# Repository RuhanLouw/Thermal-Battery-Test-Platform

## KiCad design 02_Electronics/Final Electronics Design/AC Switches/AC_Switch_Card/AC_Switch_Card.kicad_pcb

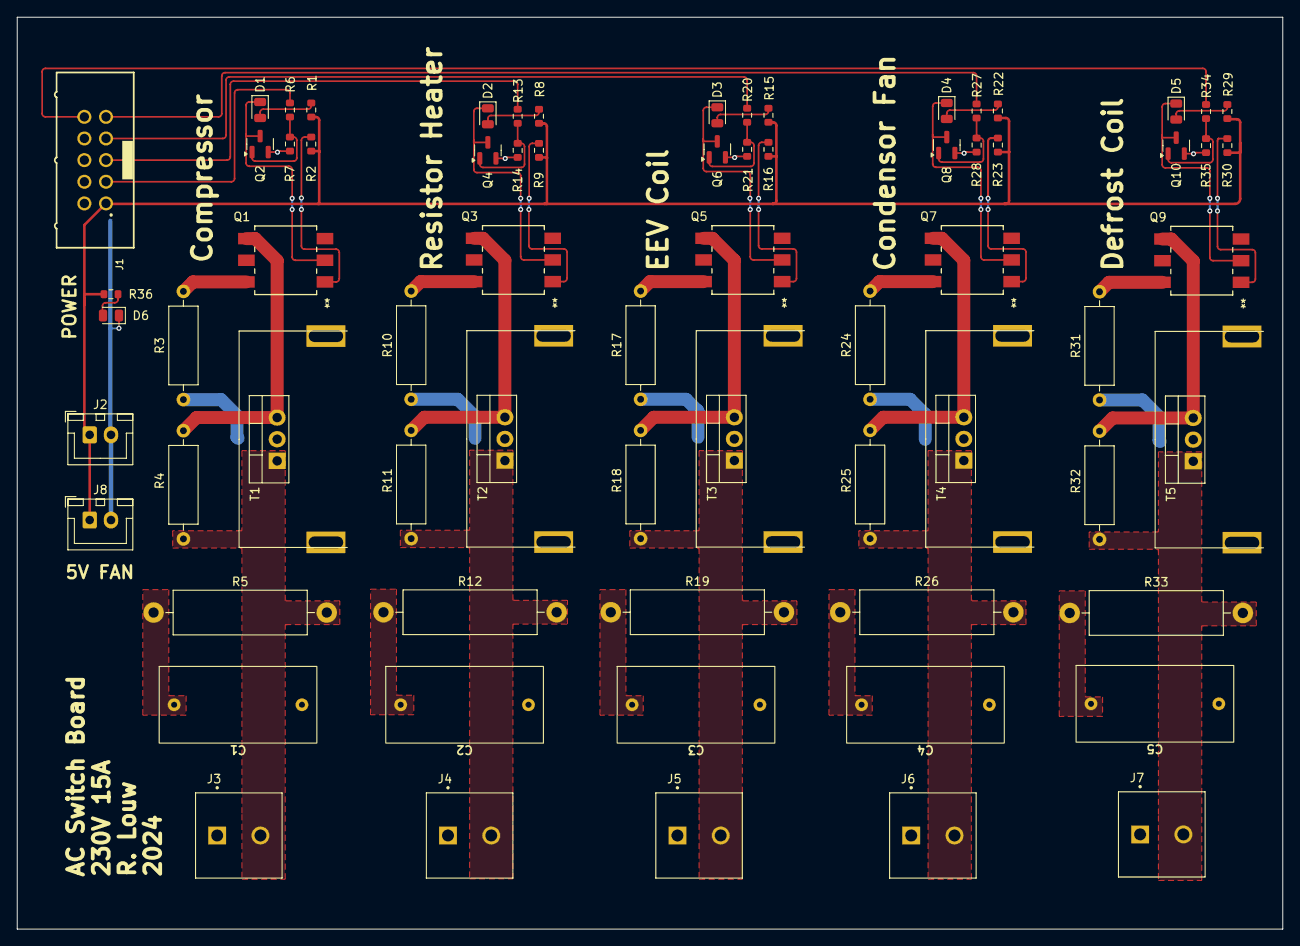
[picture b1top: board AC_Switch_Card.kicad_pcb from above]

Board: 2 copper layers, 148.5 x 107.0 mm, 70 parts (0 on the bottom side), 53 nets.

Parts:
C1, C2, C3, C4, C5: 0.22u; CAP FILM 0.22UF 10 800VDC RAD
D1, D2, D3, D4, D5, D6: LED RED CLEAR 0805 SMD; LED_0805_2012Metric
J1: Control IN; 61201021621
J2, J8: Fan; JST_XH_B2B-XH-A_1x02_P2.50mm_Vertical
J3, J4, J5, J6, J7: Screw_Terminal_01x02; TE_282857-2_screw
Q1, Q3, Q5, Q7, Q9: MOC3063S-TA1; MOC306XS_LTO
Q2, Q4, Q6, Q8, Q10: BSS138L; SOT-23
R1, R8, R15, R22, R29, R36: 145; R_0603_1608Metric
R2, R9, R16, R23, R30: 182; R_0603_1608Metric
R3, R10, R17, R24, R31: 100; R_Axial_DIN0309_L9.0mm_D3.2mm_P12.70mm_Horizontal
R4, R11, R18, R25, R32: 390; R_Axial_DIN0309_L9.0mm_D3.2mm_P12.70mm_Horizontal
R5, R12, R19, R26, R33: 51; R_Axial_DIN0516_L15.5mm_D5.0mm_P20.32mm_Horizontal
R6, R13, R20, R27, R34: 300; R_0603_1608Metric
R7, R14, R21, R28, R35: 10k; R_0603_1608Metric
T1, T2, T3, T4, T5: BT138-800E,127; HSS-B20-NPR-02 heatsink

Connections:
5V_{DD}: J1.1, J2.1, J8.1, R1.2, R2.1, R8.2, R9.1, R15.2, R16.1, R22.2, R23.1, R29.2, R30.1, R36.2
/AC_SWITCH1/230VAC: C2.2, J4.1, R10.1, T2.2
/AC_SWITCH1/LOAD: J4.2, R11.2, R12.2, T2.1
/AC_SWITCH2/230VAC: C3.2, J5.1, R17.1, T3.2
/AC_SWITCH2/LOAD: J5.2, R18.2, R19.2, T3.1
/AC_SWITCH3/230VAC: C4.2, J6.1, R24.1, T4.2
/AC_SWITCH3/LOAD: J6.2, R25.2, R26.2, T4.1
/AC_SWITCH4/230VAC: C5.2, J7.1, R31.1, T5.2
/AC_SWITCH4/LOAD: J7.2, R32.2, R33.2, T5.1
/AC_SWITCH/230VAC: C1.2, J3.1, R3.1, T1.2
/AC_SWITCH/LOAD: J3.2, R4.2, R5.2, T1.1
AC COMP ENABLE: J1.3, R6.1
AC DEFROST ENABLE: J1.10, R34.1
AC EEV COIL ENABLE: J1.7, R20.1
AC FAN ENABLE: J1.9, R27.1
AC HEATER RESISTOR ENABLE: J1.5, R13.1
GND_{DD}: D6.1 (K), J1.2, J2.2, J8.2, Q2.2 (S), Q4.2 (S), Q6.2 (S), Q8.2 (S), Q10.2 (S), R7.2, R14.2, R21.2, R28.2, R35.2
unnamed: C1.1, R5.1
unnamed: C2.1, R12.1
unnamed: C3.1, R19.1
unnamed: C4.1, R26.1
unnamed: C5.1, R33.1
unnamed: D1.2 (A), R1.1
unnamed: D1.1 (K), Q1.2, Q2.3 (D)
unnamed: D2.2 (A), R8.1
unnamed: D2.1 (K), Q3.2, Q4.3 (D)
unnamed: D3.2 (A), R15.1
unnamed: D3.1 (K), Q5.2, Q6.3 (D)
unnamed: D4.2 (A), R22.1
unnamed: D4.1 (K), Q7.2, Q8.3 (D)
unnamed: D5.2 (A), R29.1
unnamed: D5.1 (K), Q9.2, Q10.3 (D)
unnamed: D6.2 (A), R36.1
unnamed: Q1.1, R2.2
unnamed: Q1.4, R4.1, T1.3
unnamed: Q1.6, R3.2
unnamed: Q2.1 (G), R6.2, R7.1
unnamed: Q3.1, R9.2
unnamed: Q3.4, R11.1, T2.3
unnamed: Q3.6, R10.2
unnamed: Q4.1 (G), R13.2, R14.1
unnamed: Q5.1, R16.2
unnamed: Q5.4, R18.1, T3.3
unnamed: Q5.6, R17.2
unnamed: Q6.1 (G), R20.2, R21.1
unnamed: Q7.1, R23.2
unnamed: Q7.4, R25.1, T4.3
unnamed: Q7.6, R24.2
unnamed: Q8.1 (G), R27.2, R28.1
unnamed: Q9.1, R30.2
unnamed: Q9.4, R32.1, T5.3
unnamed: Q9.6, R31.2
unnamed: Q10.1 (G), R34.2, R35.1

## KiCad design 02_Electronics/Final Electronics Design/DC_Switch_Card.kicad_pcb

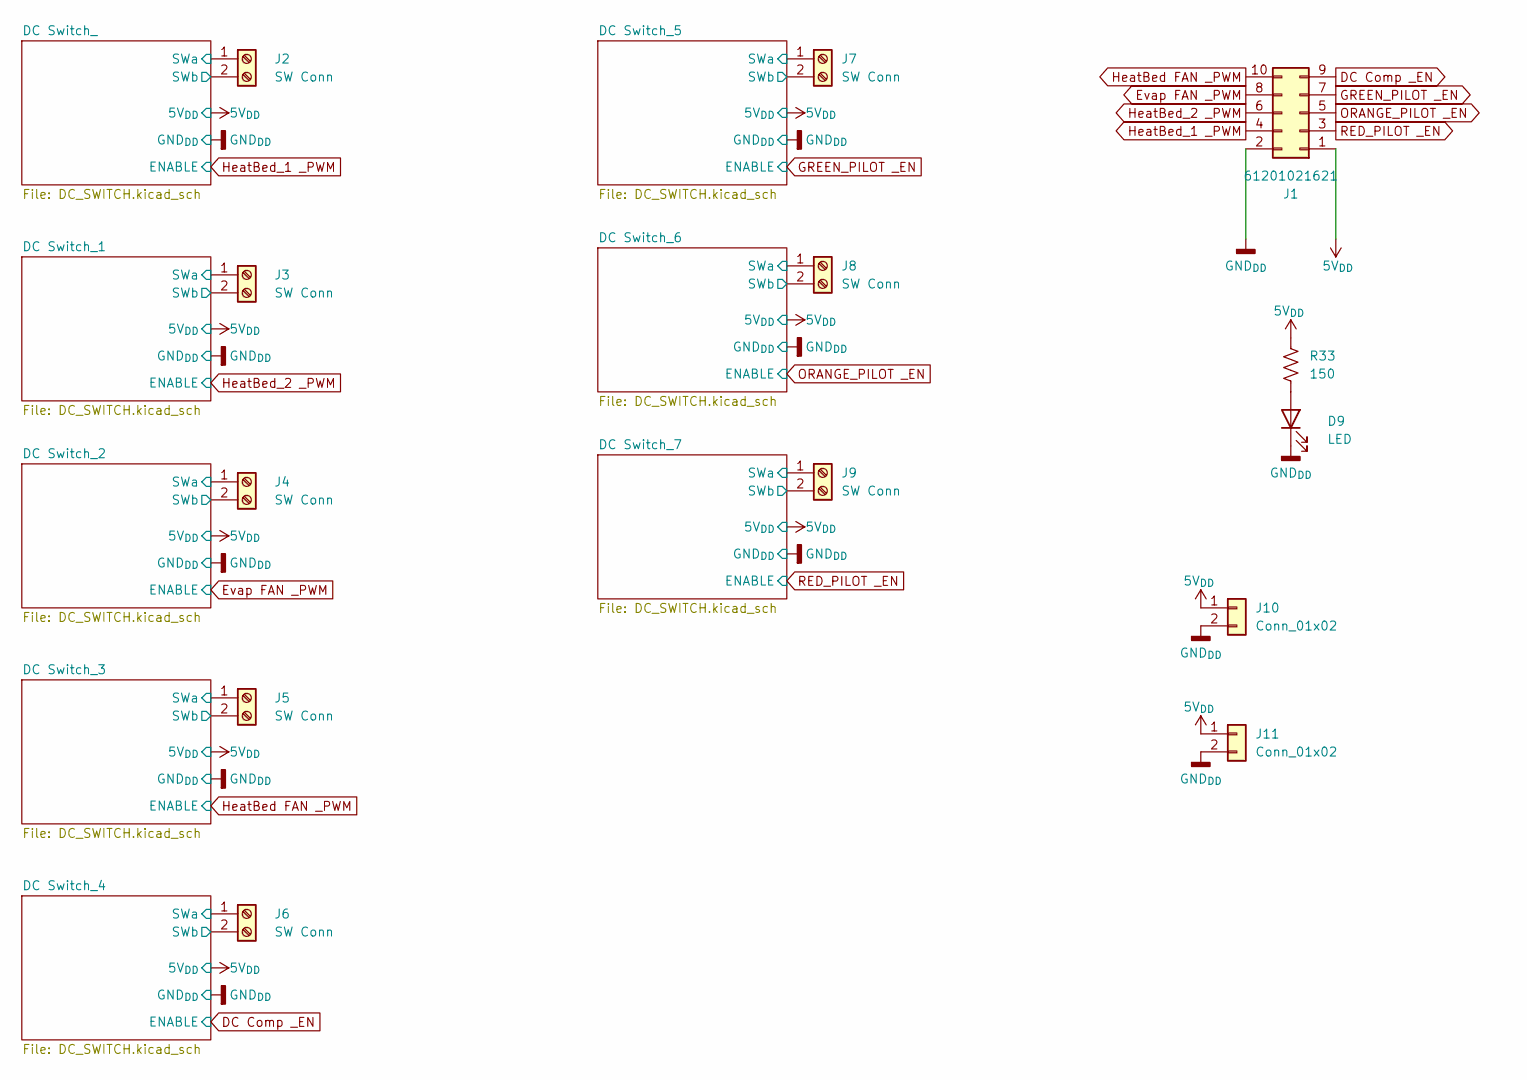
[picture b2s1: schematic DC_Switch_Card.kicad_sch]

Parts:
D9: LED; R_0805_2012Metric
J1: 61201021621
J2, J3, J4, J5, J6, J7, J8, J9: SW Conn; TE_282857-2_screw
J10, J11: Conn_01x02; JST_XH_B2B-XH-A_1x02_P2.50mm_Vertical
R33: 150; R_0603_1608Metric

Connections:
5V_{DD}: J1.1, J10.1, J11.1, R33.2; also elsewhere on the board
/DC Switch_1/SWa: J3.1; also elsewhere on the board
/DC Switch_1/SWb: J3.2; also elsewhere on the board
/DC Switch_2/SWa: J4.1; also elsewhere on the board
/DC Switch_2/SWb: J4.2; also elsewhere on the board
/DC Switch_3/SWa: J5.1; also elsewhere on the board
/DC Switch_3/SWb: J5.2; also elsewhere on the board
/DC Switch_4/SWa: J6.1; also elsewhere on the board
/DC Switch_4/SWb: J6.2; also elsewhere on the board
/DC Switch_5/SWa: J7.1; also elsewhere on the board
/DC Switch_5/SWb: J7.2; also elsewhere on the board
/DC Switch_6/SWa: J8.1; also elsewhere on the board
/DC Switch_6/SWb: J8.2; also elsewhere on the board
/DC Switch_7/SWa: J9.1; also elsewhere on the board
/DC Switch_7/SWb: J9.2; also elsewhere on the board
/DC Switch_/SWa: J2.1; also elsewhere on the board
/DC Switch_/SWb: J2.2; also elsewhere on the board
DC Comp _EN: J1.9; also elsewhere on the board
Evap FAN _PWM: J1.8; also elsewhere on the board
GND_{DD}: D9.1 (K), J1.2, J10.2, J11.2; also elsewhere on the board
GREEN_PILOT _EN: J1.7; also elsewhere on the board
HeatBed FAN _PWM: J1.10; also elsewhere on the board
HeatBed_1 _PWM: J1.4; also elsewhere on the board
HeatBed_2 _PWM: J1.6; also elsewhere on the board
unnamed: D9.2 (A), R33.1
ORANGE_PILOT _EN: J1.5; also elsewhere on the board
RED_PILOT _EN: J1.3; also elsewhere on the board

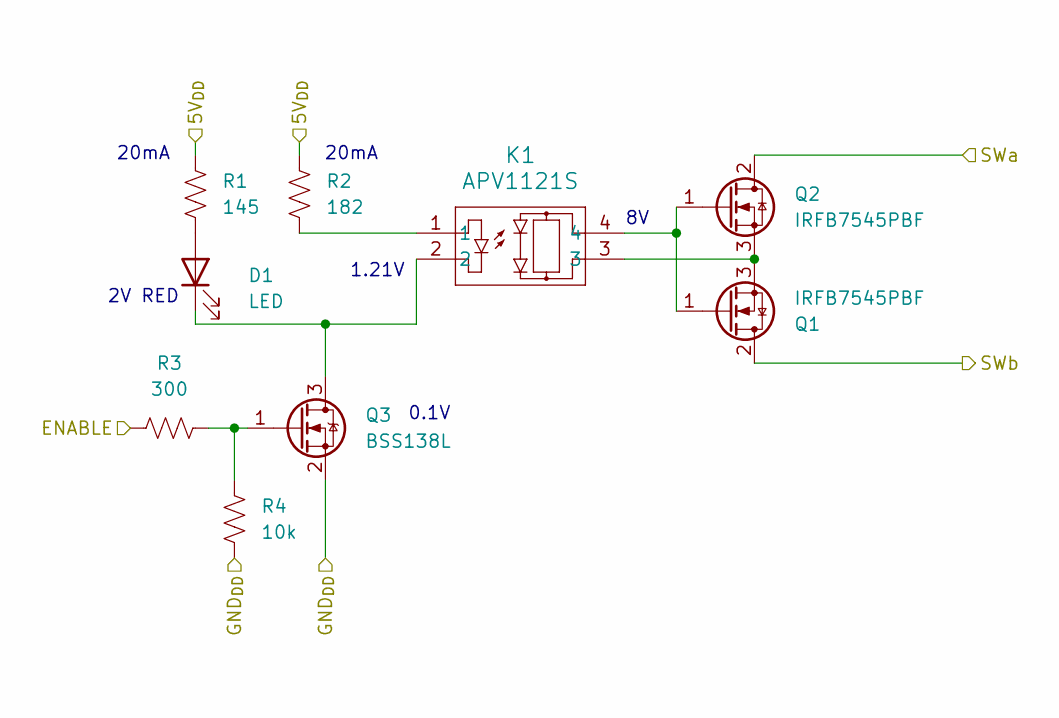
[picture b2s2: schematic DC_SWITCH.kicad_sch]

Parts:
D1: LED; R_0805_2012Metric
K1: APV1121S; SOP4PIN_PAN-M
Q1, Q2: IRFB7545PBF; TO-220-3_Vertical
Q3: BSS138L; SOT-23
R1: 145; R_0603_1608Metric
R2: 182; R_0603_1608Metric
R3: 300; R_0603_1608Metric
R4: 10k; R_0603_1608Metric

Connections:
5V_{DD}: R1.2, R2.1; also elsewhere on the board
/DC Switch_/SWa: Q2.2 (D); also elsewhere on the board
/DC Switch_/SWb: Q1.2 (D); also elsewhere on the board
GND_{DD}: Q3.2 (S), R4.2; also elsewhere on the board
HeatBed_1 _PWM: R3.1; also elsewhere on the board
unnamed: D1.2 (A), R1.1
unnamed: D1.1 (K), K1.2, Q3.3 (D)
unnamed: K1.1, R2.2
unnamed: K1.4, Q1.1 (G), Q2.1 (G)
unnamed: K1.3, Q1.3 (S), Q2.3 (S)
unnamed: Q3.1 (G), R3.2, R4.1

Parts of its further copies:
D2, D3, D4, D5, D6, D7, D8: LED; R_0805_2012Metric
K2, K3, K4, K5, K6, K7, K8: APV1121S; SOP4PIN_PAN-M
Q4, Q5, Q7, Q8, Q10, Q11, Q13, Q14, Q16, Q17, Q19, Q20, Q22, Q23: IRFB7545PBF; TO-220-3_Vertical
Q6, Q9, Q12, Q15, Q18, Q21, Q24: BSS138L; SOT-23
R5, R9, R13, R17, R21, R25, R29: 145; R_0603_1608Metric
R6, R10, R14, R18, R22, R26, R30: 182; R_0603_1608Metric
R7, R11, R15, R19, R23, R27, R31: 300; R_0603_1608Metric
R8, R12, R16, R20, R24, R28, R32: 10k; R_0603_1608Metric

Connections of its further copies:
5V_{DD}: R5.2, R6.1, R9.2, R10.1, R13.2, R14.1, R17.2, R18.1, R21.2, R22.1, R25.2, R26.1, R29.2, R30.1; also elsewhere on the board
/DC Switch_1/SWa: Q5.2 (D); also elsewhere on the board
/DC Switch_1/SWb: Q4.2 (D); also elsewhere on the board
/DC Switch_2/SWa: Q8.2 (D); also elsewhere on the board
/DC Switch_2/SWb: Q7.2 (D); also elsewhere on the board
/DC Switch_3/SWa: Q11.2 (D); also elsewhere on the board
/DC Switch_3/SWb: Q10.2 (D); also elsewhere on the board
/DC Switch_4/SWa: Q14.2 (D); also elsewhere on the board
/DC Switch_4/SWb: Q13.2 (D); also elsewhere on the board
/DC Switch_5/SWa: Q17.2 (D); also elsewhere on the board
/DC Switch_5/SWb: Q16.2 (D); also elsewhere on the board
/DC Switch_6/SWa: Q20.2 (D); also elsewhere on the board
/DC Switch_6/SWb: Q19.2 (D); also elsewhere on the board
/DC Switch_7/SWa: Q23.2 (D); also elsewhere on the board
/DC Switch_7/SWb: Q22.2 (D); also elsewhere on the board
DC Comp _EN: R19.1; also elsewhere on the board
Evap FAN _PWM: R11.1; also elsewhere on the board
GND_{DD}: Q6.2 (S), Q9.2 (S), Q12.2 (S), Q15.2 (S), Q18.2 (S), Q21.2 (S), Q24.2 (S), R8.2, R12.2, R16.2, R20.2, R24.2, R28.2, R32.2; also elsewhere on the board
GREEN_PILOT _EN: R23.1; also elsewhere on the board
HeatBed FAN _PWM: R15.1; also elsewhere on the board
HeatBed_2 _PWM: R7.1; also elsewhere on the board
unnamed: D2.2 (A), R5.1
unnamed: D2.1 (K), K2.2, Q6.3 (D)
unnamed: D3.2 (A), R9.1
unnamed: D3.1 (K), K3.2, Q9.3 (D)
unnamed: D4.2 (A), R13.1
unnamed: D4.1 (K), K4.2, Q12.3 (D)
unnamed: D5.2 (A), R17.1
unnamed: D5.1 (K), K5.2, Q15.3 (D)
unnamed: D6.2 (A), R21.1
unnamed: D6.1 (K), K6.2, Q18.3 (D)
unnamed: D7.2 (A), R25.1
unnamed: D7.1 (K), K7.2, Q21.3 (D)
unnamed: D8.2 (A), R29.1
unnamed: D8.1 (K), K8.2, Q24.3 (D)
unnamed: K2.1, R6.2
unnamed: K3.1, R10.2
unnamed: K4.1, R14.2
unnamed: K5.1, R18.2
unnamed: K6.1, R22.2
unnamed: K7.1, R26.2
unnamed: K8.1, R30.2
unnamed: K2.4, Q4.1 (G), Q5.1 (G)
unnamed: K2.3, Q4.3 (S), Q5.3 (S)
unnamed: Q6.1 (G), R7.2, R8.1
unnamed: K3.4, Q7.1 (G), Q8.1 (G)
unnamed: K3.3, Q7.3 (S), Q8.3 (S)
unnamed: Q9.1 (G), R11.2, R12.1
unnamed: K4.4, Q10.1 (G), Q11.1 (G)
unnamed: K4.3, Q10.3 (S), Q11.3 (S)
unnamed: Q12.1 (G), R15.2, R16.1
unnamed: K5.4, Q13.1 (G), Q14.1 (G)
unnamed: K5.3, Q13.3 (S), Q14.3 (S)
unnamed: Q15.1 (G), R19.2, R20.1
unnamed: K6.4, Q16.1 (G), Q17.1 (G)
unnamed: K6.3, Q16.3 (S), Q17.3 (S)
unnamed: Q18.1 (G), R23.2, R24.1
unnamed: K7.4, Q19.1 (G), Q20.1 (G)
unnamed: K7.3, Q19.3 (S), Q20.3 (S)
unnamed: Q21.1 (G), R27.2, R28.1
unnamed: K8.4, Q22.1 (G), Q23.1 (G)
unnamed: K8.3, Q22.3 (S), Q23.3 (S)
unnamed: Q24.1 (G), R31.2, R32.1
ORANGE_PILOT _EN: R27.1; also elsewhere on the board
RED_PILOT _EN: R31.1; also elsewhere on the board

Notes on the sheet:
0.1V
20mA
1.21V
2V RED

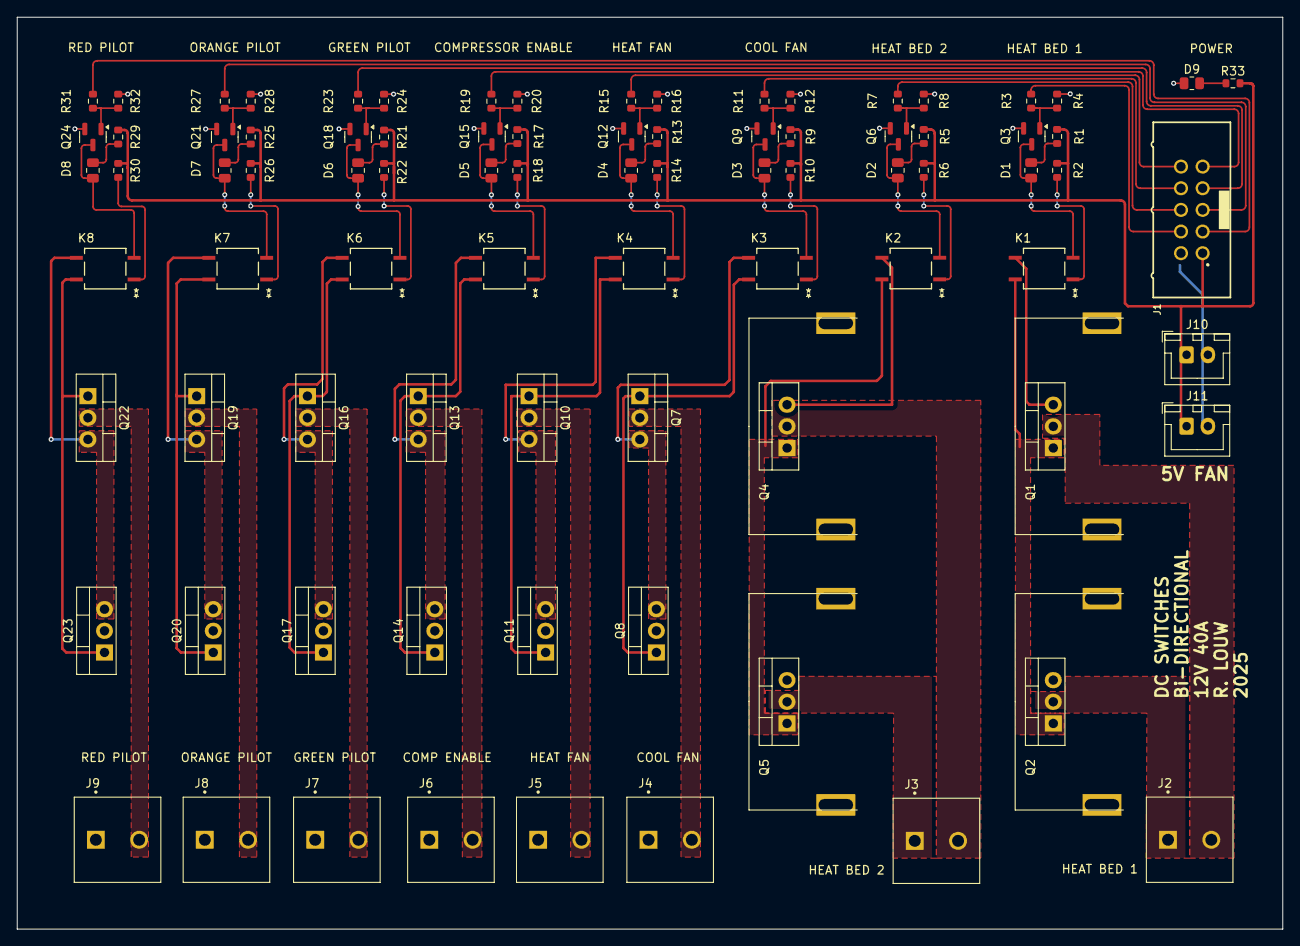
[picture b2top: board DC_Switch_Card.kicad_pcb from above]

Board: 2 copper layers, 148.5 x 107.0 mm, 85 parts (0 on the bottom side), 75 nets.

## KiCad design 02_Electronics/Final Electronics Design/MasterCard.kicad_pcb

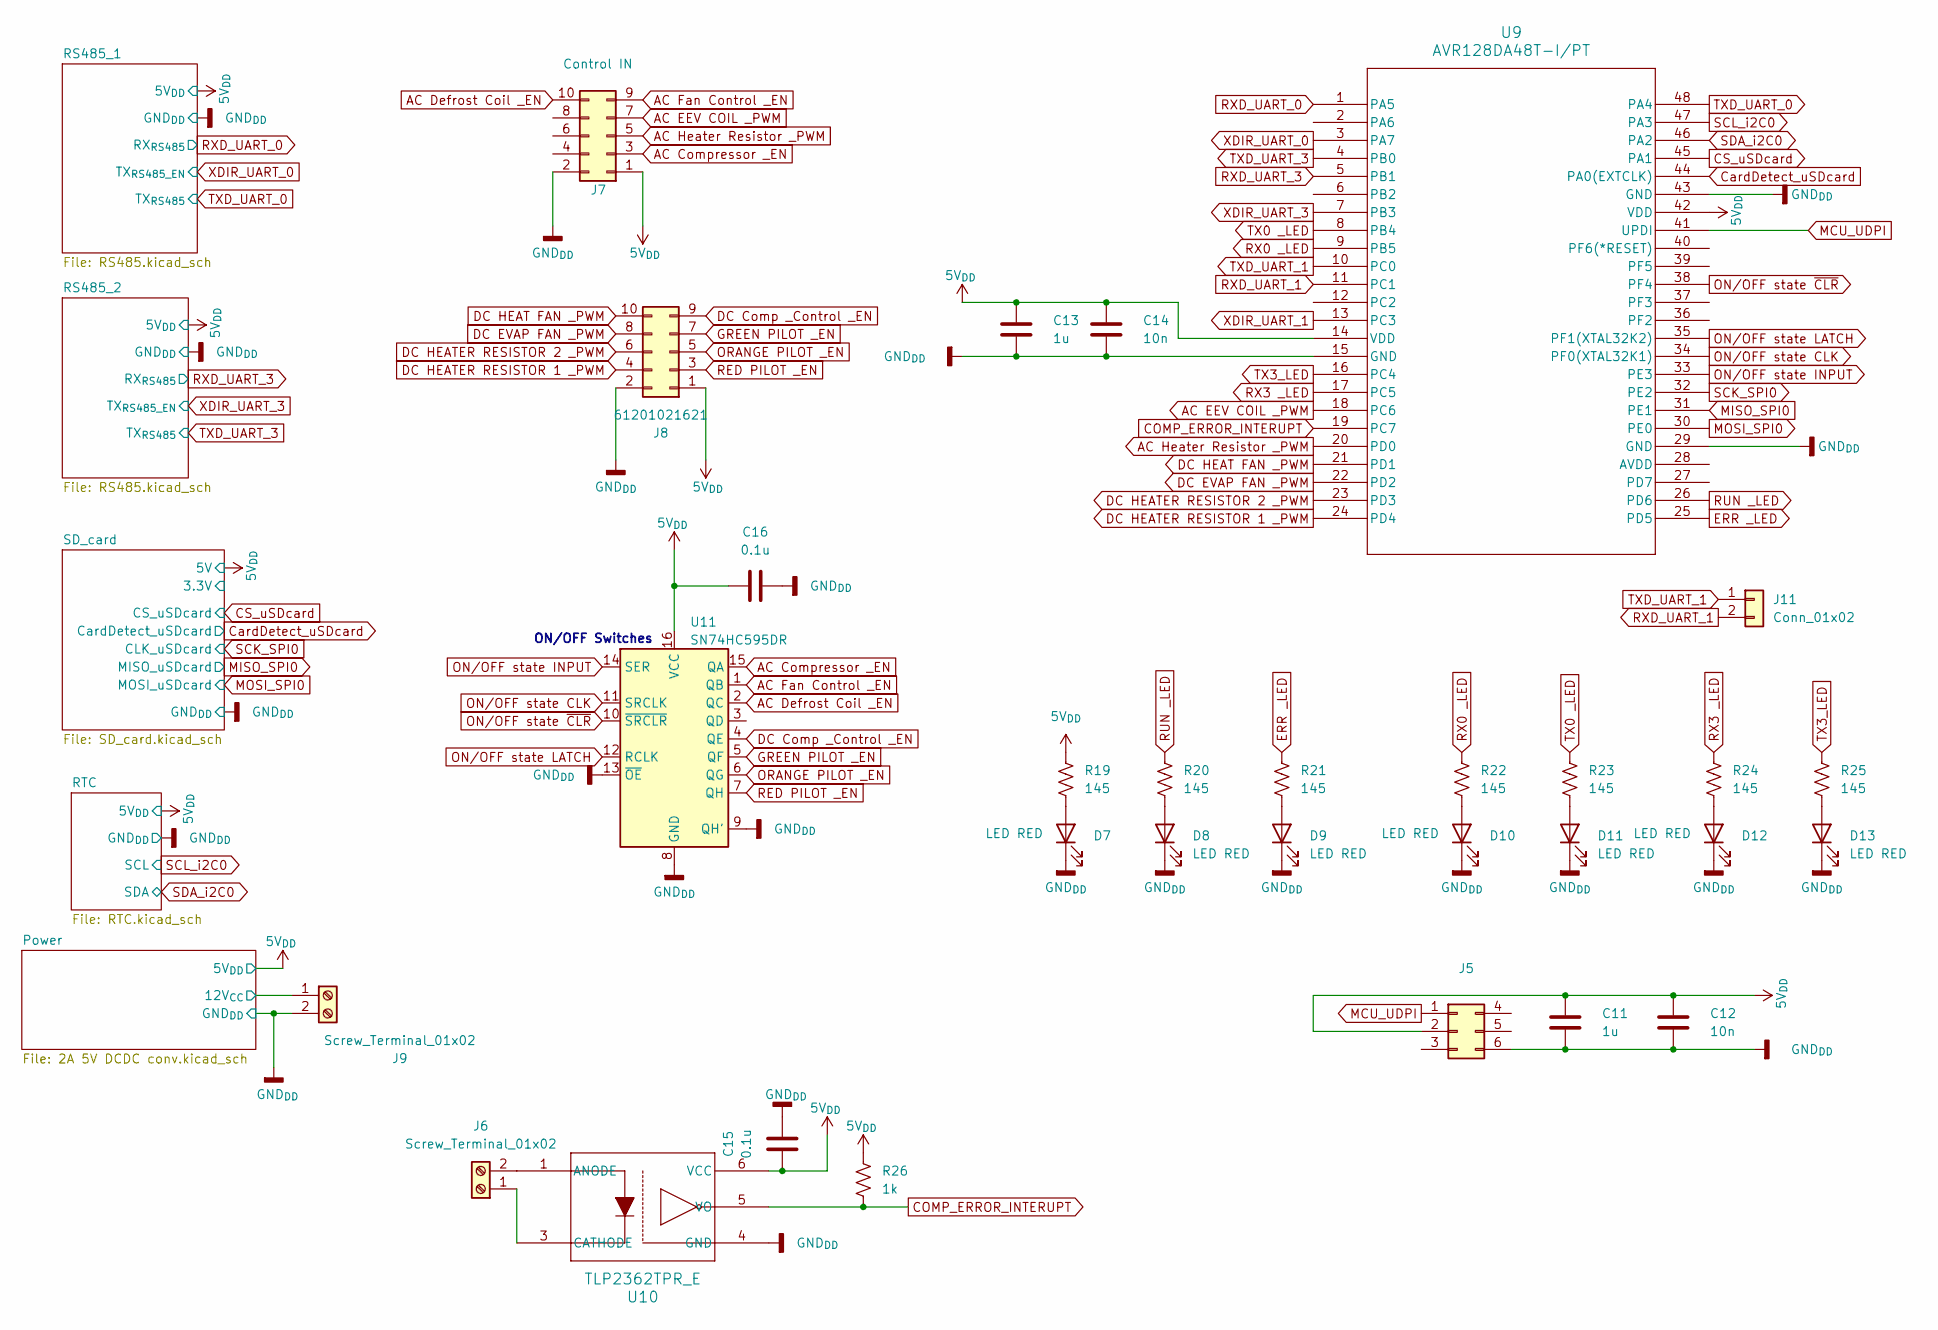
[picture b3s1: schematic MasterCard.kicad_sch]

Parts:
C11, C13: 1u; C_0603_1608Metric
C12, C14: 10n; C_0603_1608Metric
C15, C16: 0.1u; C_0603_1608Metric
D7, D8, D9, D10, D11, D12, D13: LED RED; LED_0805_2012Metric
J5: Conn_02x03_Top_Bottom; 61200621621
J6, J9: Screw_Terminal_01x02; TE_282857-2_screw
J7: Control IN; 61201021621
J8: 61201021621
J11: Conn_01x02; PinHeader_1x02_P2.54mm_Vertical
R19, R20, R21, R22, R23, R24, R25: 145; R_0603_1608Metric
R26: 1k; R_0603_1608Metric
U9: AVR128DA48T-I/PT; TQFP48_PT_MCH
U10: TLP2362TPR_E; TLP2362(TPR,E
U11: SN74HC595DR; SOIC-16_3.9x9.9mm_P1.27mm

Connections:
5V_{DD}: C11.1, C12.1, C13.1, C14.1, C15.1, C16.1, J5.2, J7.1, J8.1, R19.2, R26.1, U9.14 (VDD), U9.42 (VDD), U10.6 (VCC), U11.16 (VCC); also elsewhere on the board
/Power/12V_{CC}: J9.1; also elsewhere on the board
AC Compressor _EN: J7.3, U11.15 (QA)
AC Defrost Coil _EN: J7.10, U11.2 (QC)
AC EEV COIL _PWM: J7.7, U9.18 (PC6)
AC Fan Control _EN: J7.9, U11.1 (QB)
AC Heater Resistor _PWM: J7.5, U9.20 (PD0)
COMP_ERROR_INTERUPT: R26.2, U9.19 (PC7), U10.5 (VO)
CS_uSDcard: U9.45 (PA1); also elsewhere on the board
CardDetect_uSDcard: U9.44 (PA0(EXTCLK)); also elsewhere on the board
DC Comp _Control _EN: J8.9, U11.4 (QE)
DC EVAP FAN _PWM: J8.8, U9.22 (PD2)
DC HEAT FAN _PWM: J8.10, U9.21 (PD1)
DC HEATER RESISTOR 1 _PWM: J8.4, U9.24 (PD4)
DC HEATER RESISTOR 2 _PWM: J8.6, U9.23 (PD3)
ERR _LED: R21.2, U9.25 (PD5)
GND_{DD}: C11.2, C12.2, C13.2, C14.2, C15.2, C16.2, D7.1 (K), D8.1 (K), D9.1 (K), D10.1 (K), D11.1 (K), D12.1 (K), D13.1 (K), J5.6, J7.2, J8.2, J9.2, U9.15 (GND), U9.29 (GND), U9.43 (GND), U10.4 (GND), U11.8 (GND), U11.9 (QH'), U11.13 (~OE); also elsewhere on the board
GREEN PILOT _EN: J8.7, U11.5 (QF)
MCU_UDPI: J5.1, U9.41 (UPDI)
MISO_SPI0: U9.31 (PE1); also elsewhere on the board
MOSI_SPI0: U9.30 (PE0); also elsewhere on the board
unnamed: D7.2 (A), R19.1
unnamed: D8.2 (A), R20.1
unnamed: D9.2 (A), R21.1
unnamed: D10.2 (A), R22.1
unnamed: D11.2 (A), R23.1
unnamed: D12.2 (A), R24.1
unnamed: D13.2 (A), R25.1
unnamed: J6.1, U10.3 (CATHODE)
unnamed: J6.2, U10.1 (ANODE)
ON/OFF state CLK: U9.34 (PF0(XTAL32K1)), U11.11 (SRCLK)
ON/OFF state INPUT: U9.33 (PE3), U11.14 (SER)
ON/OFF state LATCH: U9.35 (PF1(XTAL32K2)), U11.12 (RCLK)
ON/OFF state ~CLR: U9.38 (PF4), U11.10 (~SRCLR)
ORANGE PILOT _EN: J8.5, U11.6 (QG)
RED PILOT _EN: J8.3, U11.7 (QH)
RUN _LED: R20.2, U9.26 (PD6)
RX0 _LED: R22.2, U9.9 (PB5)
RX3 _LED: R24.2, U9.17 (PC5)
RXD_UART_0: U9.1 (PA5); also elsewhere on the board
RXD_UART_1: J11.2, U9.11 (PC1)
RXD_UART_3: U9.5 (PB1); also elsewhere on the board
SCK_SPI0: U9.32 (PE2); also elsewhere on the board
SCL_i2C0: U9.47 (PA3); also elsewhere on the board
SCL_i2C1: U9.37 (PF3)
SDA_i2C0: U9.46 (PA2); also elsewhere on the board
SDA_i2C1: U9.36 (PF2)
TX0 _LED: R23.2, U9.8 (PB4)
TX3_LED: R25.2, U9.16 (PC4)
TXD_UART_0: U9.48 (PA4); also elsewhere on the board
TXD_UART_1: J11.1, U9.10 (PC0)
TXD_UART_3: U9.4 (PB0); also elsewhere on the board
XDIR_UART_0: U9.3 (PA7); also elsewhere on the board
XDIR_UART_1: U9.13 (PC3)
XDIR_UART_3: U9.7 (PB3); also elsewhere on the board

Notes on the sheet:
ON/OFF Switches

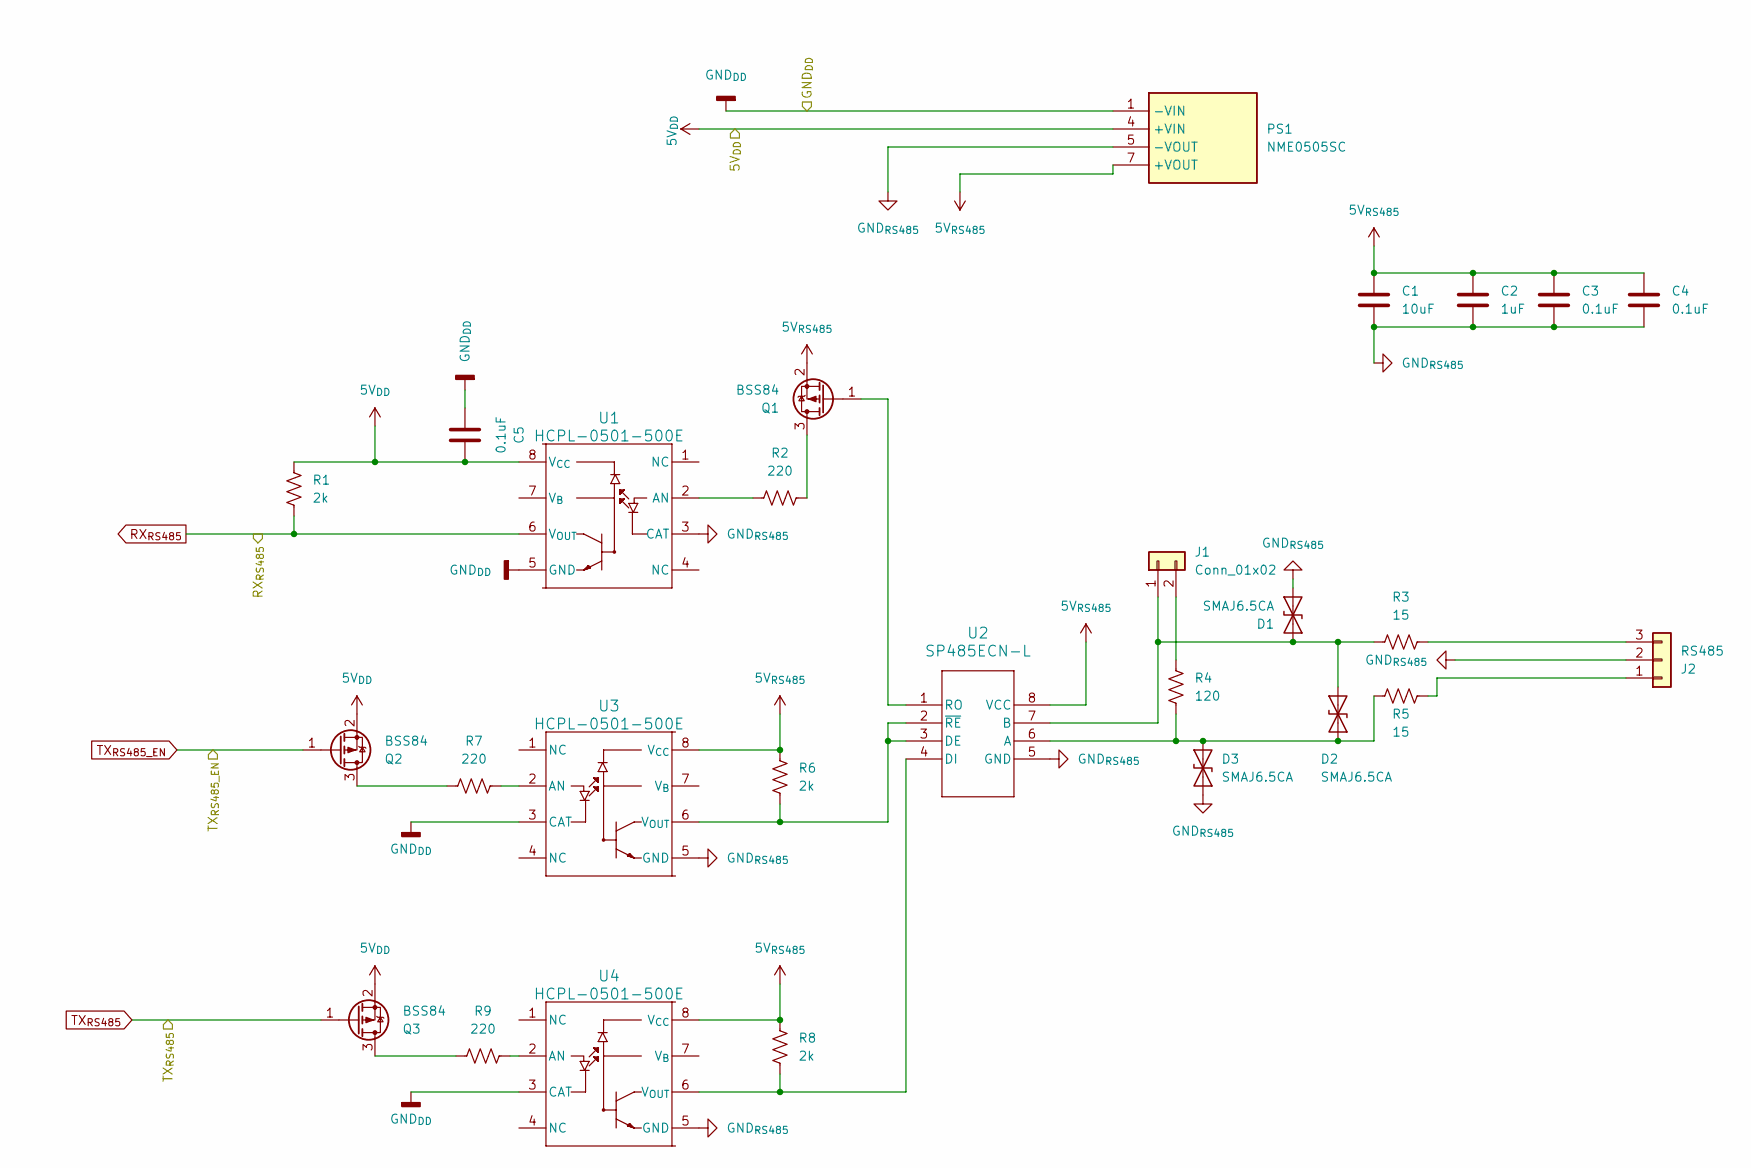
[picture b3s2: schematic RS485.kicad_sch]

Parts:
C1: 10uF; C_0805_2012Metric
C2: 1uF; C_0603_1608Metric
C3, C4, C5: 0.1uF; C_0603_1608Metric
D1, D2, D3: SMAJ6.5CA; D_SMA
J1: Conn_01x02; PinHeader_1x02_P2.54mm_Vertical
J2: RS485; TE_282857-3_screw
PS1: NME0505SC; Mouser Part Number 580-NME0505SC
Q1, Q2, Q3: BSS84; SOT-23
R1, R6, R8: 2k; R_0603_1608Metric
R2, R7, R9: 220; R_0603_1608Metric
R3, R5: 15; R_1206_3216Metric
R4: 120; R_0603_1608Metric
U1, U3, U4: HCPL-0501-500E; SO8_HCPL-0501-500_BRA
U2: SP485ECN-L; NSOIC-8

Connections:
5V_{DD}: C5.2, PS1.4 (+VIN), Q2.2 (S), Q3.2 (S), R1.2, U1.8 (V_{CC}); also elsewhere on the board
5V_{RS485}: C1.1, C2.1, C3.1, C4.1, PS1.7 (+VOUT), Q1.2 (S), R6.2, R8.2, U2.8 (VCC), U3.8 (V_{CC}), U4.8 (V_{CC}); also elsewhere on the board
GND_{DD}: C5.1, PS1.1 (-VIN), U1.5 (GND), U3.3 (CAT), U4.3 (CAT); also elsewhere on the board
GND_{RS485}: C1.2, C2.2, C3.2, C4.2, D1.1 (A1), D3.1 (A1), J2.2, PS1.5 (-VOUT), U1.3 (CAT), U2.5 (GND), U3.5 (GND), U4.5 (GND); also elsewhere on the board
unnamed: D1.2 (A2), D2.1 (A1), J1.1, R3.1, U2.7 (B)
unnamed: D2.2 (A2), D3.2 (A2), R4.2, R5.1, U2.6 (A)
unnamed: J1.2, R4.1
unnamed: J2.1, R5.2
unnamed: J2.3, R3.2
unnamed: Q1.3 (D), R2.1
unnamed: Q1.1 (G), U2.1 (RO)
unnamed: Q2.3 (D), R7.1
unnamed: Q3.3 (D), R9.1
unnamed: R2.2, U1.2 (AN)
unnamed: R6.1, U2.2 (~RE), U2.3 (DE), U3.6 (V_{OUT})
unnamed: R8.1, U2.4 (DI), U4.6 (V_{OUT})
unnamed: R7.2, U3.2 (AN)
unnamed: R9.2, U4.2 (AN)
RXD_UART_0: R1.1, U1.6 (V_{OUT}); also elsewhere on the board
TXD_UART_0: Q3.1 (G); also elsewhere on the board
XDIR_UART_0: Q2.1 (G); also elsewhere on the board

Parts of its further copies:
C6: 10uF; C_0805_2012Metric
C7: 1uF; C_0603_1608Metric
C8, C9, C10: 0.1uF; C_0603_1608Metric
D4, D5, D6: SMAJ6.5CA; D_SMA
J3: Conn_01x02; PinHeader_1x02_P2.54mm_Vertical
J4: RS485; TE_282857-3_screw
PS2: NME0505SC; Mouser Part Number 580-NME0505SC
Q4, Q5, Q6: BSS84; SOT-23
R10, R15, R17: 2k; R_0603_1608Metric
R11, R16, R18: 220; R_0603_1608Metric
R12, R14: 15; R_1206_3216Metric
R13: 120; R_0603_1608Metric
U5, U7, U8: HCPL-0501-500E; SO8_HCPL-0501-500_BRA
U6: SP485ECN-L; NSOIC-8

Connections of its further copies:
5V_{DD}: C10.2, PS2.4 (+VIN), Q5.2 (S), Q6.2 (S), R10.2, U5.8 (V_{CC}); also elsewhere on the board
5V_{RS485}: C6.1, C7.1, C8.1, C9.1, PS2.7 (+VOUT), Q4.2 (S), R15.2, R17.2, U6.8 (VCC), U7.8 (V_{CC}), U8.8 (V_{CC}); also elsewhere on the board
GND_{DD}: C10.1, PS2.1 (-VIN), U5.5 (GND), U7.3 (CAT), U8.3 (CAT); also elsewhere on the board
GND_{RS485}: C6.2, C7.2, C8.2, C9.2, D4.1 (A1), D6.1 (A1), J4.2, PS2.5 (-VOUT), U5.3 (CAT), U6.5 (GND), U7.5 (GND), U8.5 (GND); also elsewhere on the board
unnamed: D4.2 (A2), D5.1 (A1), J3.1, R12.1, U6.7 (B)
unnamed: D5.2 (A2), D6.2 (A2), R13.2, R14.1, U6.6 (A)
unnamed: J3.2, R13.1
unnamed: J4.1, R14.2
unnamed: J4.3, R12.2
unnamed: Q4.3 (D), R11.1
unnamed: Q4.1 (G), U6.1 (RO)
unnamed: Q5.3 (D), R16.1
unnamed: Q6.3 (D), R18.1
unnamed: R11.2, U5.2 (AN)
unnamed: R15.1, U6.2 (~RE), U6.3 (DE), U7.6 (V_{OUT})
unnamed: R17.1, U6.4 (DI), U8.6 (V_{OUT})
unnamed: R16.2, U7.2 (AN)
unnamed: R18.2, U8.2 (AN)
RXD_UART_3: R10.1, U5.6 (V_{OUT}); also elsewhere on the board
TXD_UART_3: Q6.1 (G); also elsewhere on the board
XDIR_UART_3: Q5.1 (G); also elsewhere on the board

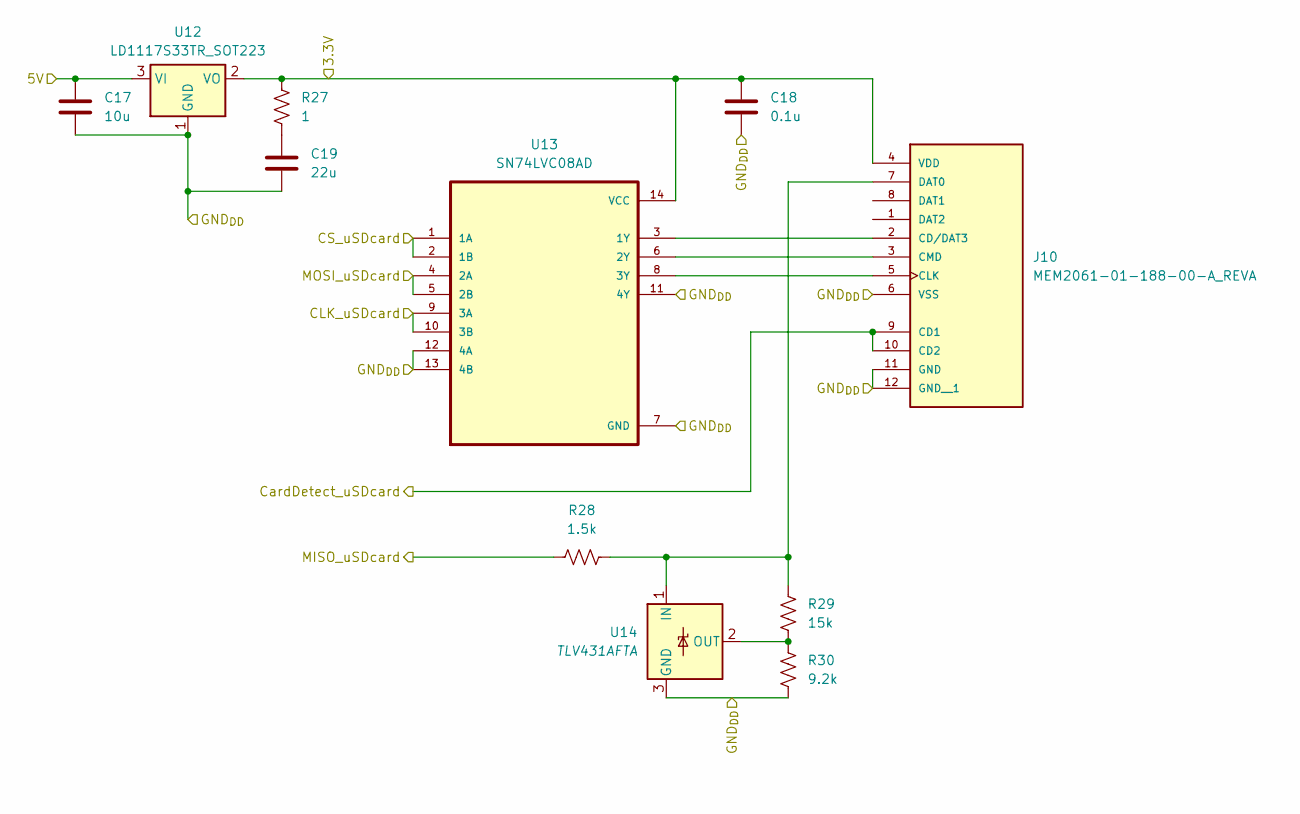
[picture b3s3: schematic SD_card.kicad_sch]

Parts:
C17: 10u; C_0603_1608Metric
C18: 0.1u; C_0603_1608Metric
C19: 22u; C_1206_3216Metric
J10: MEM2061-01-188-00-A_REVA; GCT_MEM2061-01-188-00-A_REVA
R27: 1; R_0603_1608Metric
R28: 1.5k; R_0603_1608Metric
R29: 15k; R_0603_1608Metric
R30: 9.2k; R_0603_1608Metric
U12: LD1117S33TR_SOT223; SOT-223-3_TabPin2
U13: SN74LVC08AD
U14: TLV431AFTA; SOT-23

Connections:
5V_{DD}: C17.1, U12.3 (VI); also elsewhere on the board
/SD_card/3.3V: C18.1, J10.4 (VDD), R27.2, U12.2 (VO), U13.14 (VCC)
CS_uSDcard: U13.1 (1A), U13.2 (1B); also elsewhere on the board
CardDetect_uSDcard: J10.9 (CD1), J10.10 (CD2); also elsewhere on the board
GND_{DD}: C17.2, C18.2, C19.2, J10.6 (VSS), J10.11 (GND), J10.12 (GND__1), R30.1, U12.1 (GND), U13.7 (GND), U13.11 (4Y), U13.12 (4A), U13.13 (4B), U14.3 (GND); also elsewhere on the board
MISO_SPI0: R28.1; also elsewhere on the board
MOSI_SPI0: U13.4 (2A), U13.5 (2B); also elsewhere on the board
unnamed: C19.1, R27.1
unnamed: J10.2 (CD/DAT3), U13.3 (1Y)
unnamed: J10.5 (CLK), U13.8 (3Y)
unnamed: J10.3 (CMD), U13.6 (2Y)
unnamed: J10.7 (DAT0), R28.2, R29.2, U14.1 (IN)
unnamed: R29.1, R30.2, U14.2 (OUT)
SCK_SPI0: U13.9 (3A), U13.10 (3B); also elsewhere on the board

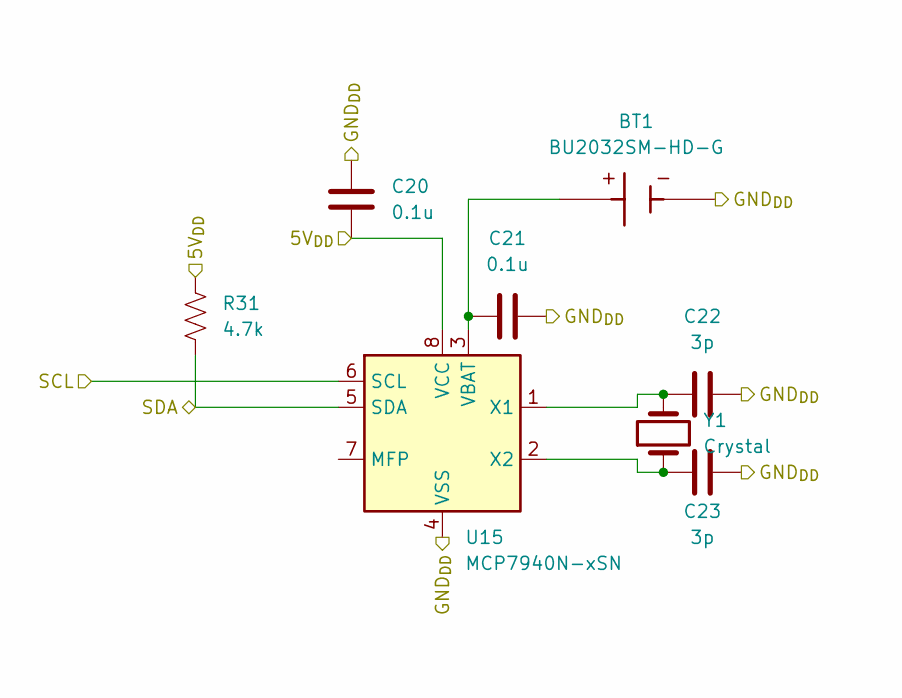
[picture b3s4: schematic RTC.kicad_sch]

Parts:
BT1: BU2032SM-HD-G; BAT_BU2032SM-HD-G; PARTREV 01/27/17
C20, C21: 0.1u; C_0603_1608Metric
C22, C23: 3p; C_0402_1005Metric_Pad0.74x0.62mm_HandSolder
R31: 4.7k; R_0603_1608Metric
U15: MCP7940N-xSN; SOIC-8_3.9x4.9mm_P1.27mm
Y1: Crystal; Crystal_Round_D2.0mm_Vertical

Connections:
5V_{DD}: C20.1, R31.1, U15.8 (VCC); also elsewhere on the board
GND_{DD}: BT1.-, C20.2, C21.2, C22.2, C23.2, U15.4 (VSS); also elsewhere on the board
unnamed: BT1.+, C21.1, U15.3 (VBAT)
unnamed: C22.1, U15.1 (X1), Y1.2
unnamed: C23.1, U15.2 (X2), Y1.1
SCL_i2C0: U15.6 (SCL); also elsewhere on the board
SDA_i2C0: R31.2, U15.5 (SDA); also elsewhere on the board

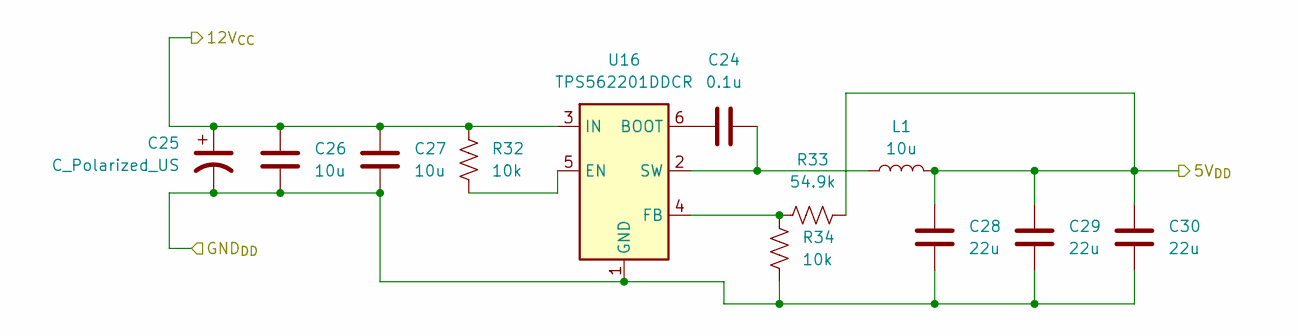
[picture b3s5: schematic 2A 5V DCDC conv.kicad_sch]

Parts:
C24: 0.1u; C_0603_1608Metric
C25: C_Polarized_US; CAP_EEFK_D_PAN
C26, C27: 10u; C_1206_3216Metric
C28, C29, C30: 22u; C_1206_3216Metric
L1: 10u; L_Bourns_SRR1208_12.7x12.7mm__
R32, R34: 10k; R_0603_1608Metric
R33: 54.9k; R_0603_1608Metric
U16: TPS562201DDCR; TSOT-23-6; Part Number TPS562201DDCR

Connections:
5V_{DD}: C28.1, C29.1, C30.1, L1.2, R33.2; also elsewhere on the board
/Power/12V_{CC}: C25.1, C26.1, C27.1, R32.1, U16.3 (IN); also elsewhere on the board
GND_{DD}: C25.2, C26.2, C27.2, C28.2, C29.2, C30.2, R34.2, U16.1 (GND); also elsewhere on the board
unnamed: C24.1, U16.6 (BOOT)
unnamed: R32.2, U16.5 (EN)
unnamed: R33.1, R34.1, U16.4 (FB)
unnamed: C24.2, L1.1, U16.2 (SW)
